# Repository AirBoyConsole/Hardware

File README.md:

# Hardware

|revision|sound|input|EEPROM|
|:---:|:---:|:---:|:---:|
| A | PCM5100A + LM4936 | MCP23008 | 128kb |

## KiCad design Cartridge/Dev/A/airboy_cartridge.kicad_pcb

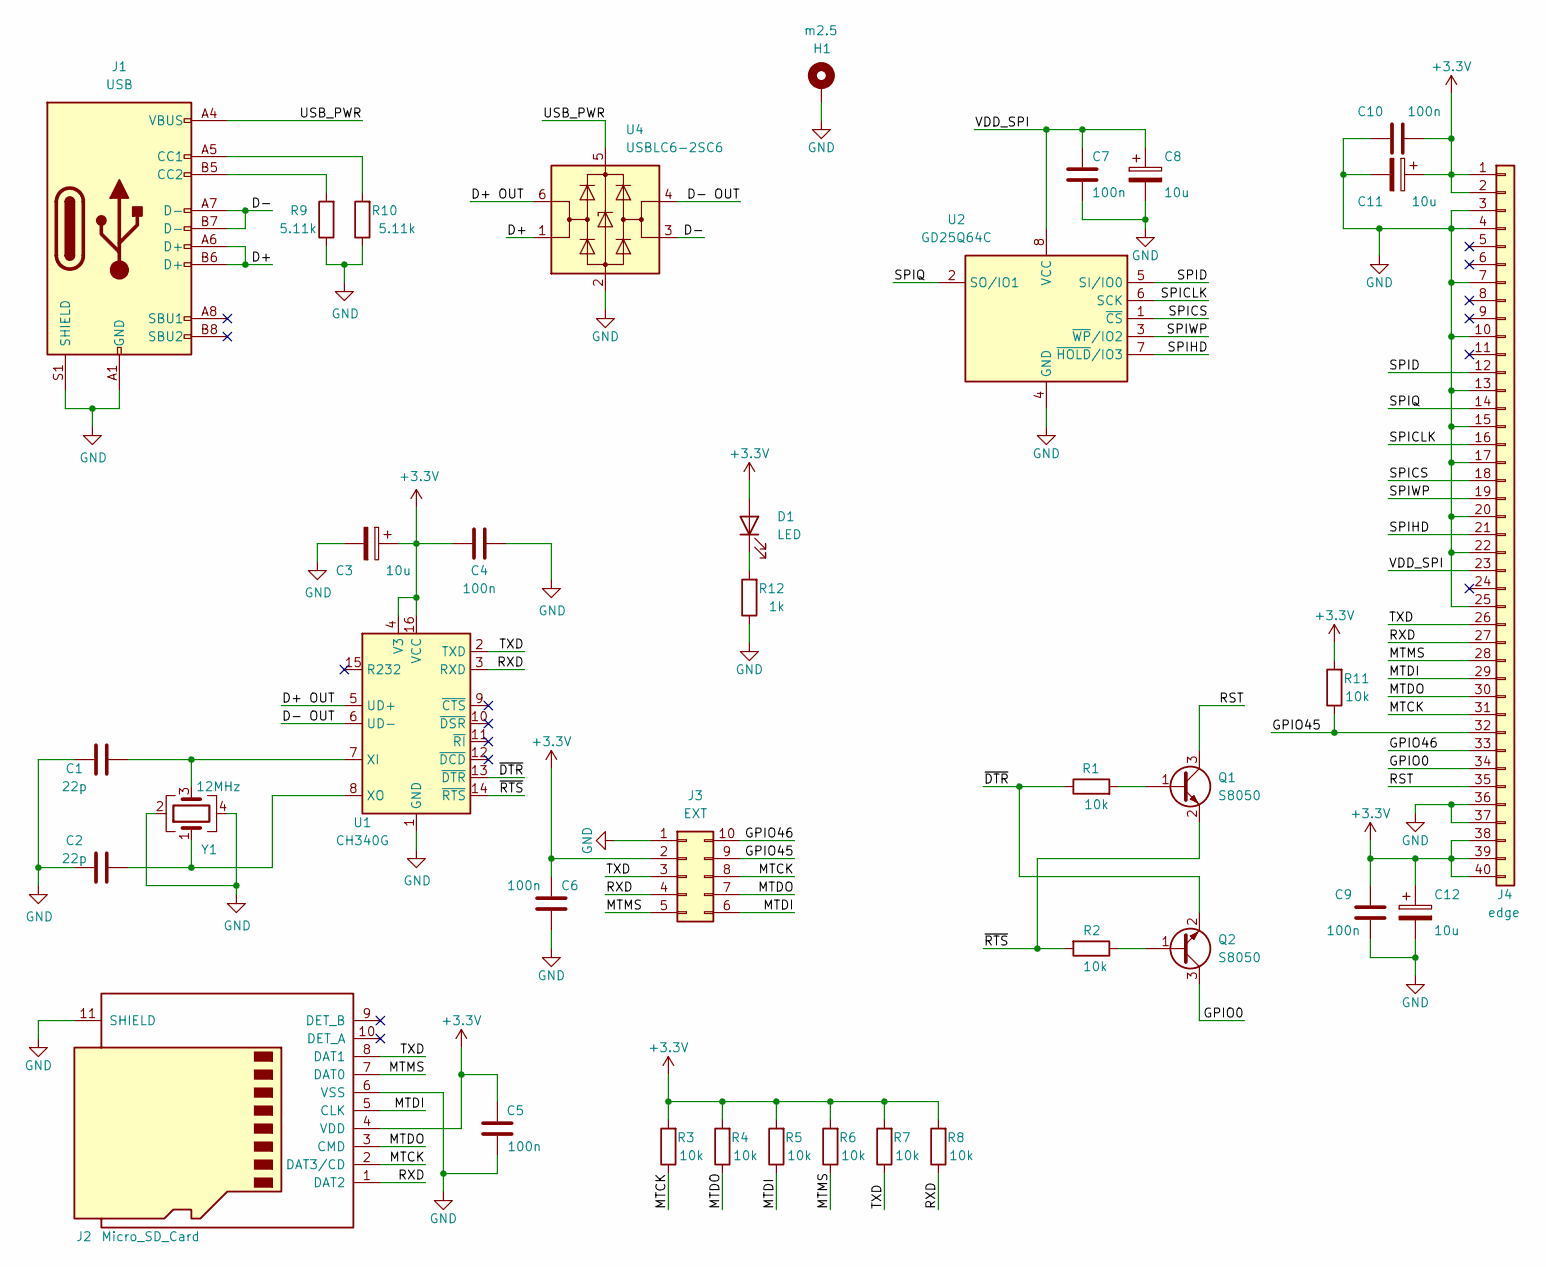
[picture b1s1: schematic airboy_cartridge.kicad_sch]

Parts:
C1, C2: 22p; C_0603_1608Metric_Pad1.08x0.95mm_HandSolder
C3, C8, C11, C12: 10u; CP_EIA-3216-18_Kemet-A_Pad1.58x1.35mm_HandSolder
C4, C5, C6, C7, C9, C10: 100n; C_0603_1608Metric_Pad1.08x0.95mm_HandSolder
D1: LED; LED_0603_1608Metric_Pad1.05x0.95mm_HandSolder
H1: m2.5; MountingHole_2.7mm_M2.5_Pad
J1: USB; USB_C_Receptacle_Palconn_UTC16-G
J2: Micro_SD_Card; microSD_HC_Hirose_DM3D-SF
J3: EXT; PinHeader_2x05_P2.54mm_Vertical
J4: edge; Connector
Q1, Q2: S8050; SOT-23
R1, R2, R3, R4, R5, R6, R7, R8, R11: 10k; R_0603_1608Metric_Pad0.98x0.95mm_HandSolder
R9, R10: 5.11k; R_0603_1608Metric_Pad0.98x0.95mm_HandSolder
R12: 1k; R_0603_1608Metric_Pad0.98x0.95mm_HandSolder
U1: CH340G; SOIC-16_3.9x9.9mm_P1.27mm
U2: GD25Q64C; SOP-8_5.28x5.23mm_P1.27mm
U4: USBLC6-2SC6; SOT-23-6
Y1: 12MHz; Crystal_SMD_5032-4Pin_5.0x3.2mm

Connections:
+3.3V: C3.1, C4.1, C5.1, C6.1, C9.2, C10.2, C11.1, C12.1, D1.2 (A), J2.4 (VDD), J3.2, J4.1, J4.2, J4.38, J4.39, J4.40, R3.2, R4.2, R5.2, R6.2, R7.2, R8.2, R11.2, U1.4 (V3), U1.16 (VCC)
/D+: J1.A6 (D+), J1.B6 (D+), U4.1 (I/O1)
/D+ OUT: U1.5 (UD+), U4.6 (I/O1)
/D-: J1.A7 (D-), J1.B7 (D-), U4.3 (I/O2)
/D- OUT: U1.6 (UD-), U4.4 (I/O2)
/GPIO0: J4.34, Q2.3 (C)
/GPIO45: J3.9, J4.32, R11.1
/GPIO46: J3.10, J4.33
/MTCK: J2.2 (DAT3/CD), J3.8, J4.31, R3.1
/MTDI: J2.5 (CLK), J3.6, J4.29, R5.1
/MTDO: J2.3 (CMD), J3.7, J4.30, R4.1
/MTMS: J2.7 (DAT0), J3.5, J4.28, R6.1
/RST: J4.35, Q1.3 (C)
/RXD: J2.1 (DAT2), J3.4, J4.27, R8.1, U1.3 (RXD)
/SPICLK: J4.16, U2.6 (SCK)
/SPICS: J4.18, U2.1 (~CS)
/SPID: J4.12, U2.5 (SI/IO0)
/SPIHD: J4.21, U2.7 (~HOLD/IO3)
/SPIQ: J4.14, U2.2 (SO/IO1)
/SPIWP: J4.19, U2.3 (~WP/IO2)
/TXD: J2.8 (DAT1), J3.3, J4.26, R7.1, U1.2 (TXD)
/USB_PWR: J1.A4 (VBUS), J1.A9 (VBUS), J1.B4 (VBUS), J1.B9 (VBUS), U4.5 (VBUS)
/VDD_SPI: C7.1, C8.1, J4.23, U2.8 (VCC)
/~DTR: Q2.2 (E), R1.1, U1.13 (~DTR)
/~RTS: Q1.2 (E), R2.2, U1.14 (~RTS)
GND: C1.2, C2.2, C3.2, C4.2, C5.2, C6.2, C7.2, C8.2, C9.1, C10.1, C11.2, C12.2, H1.1, J1.A1 (GND), J1.A12 (GND), J1.B1 (GND), J1.B12 (GND), J1.S1 (SHIELD), J2.6 (VSS), J2.11 (SHIELD), J3.1, J4.3, J4.4, J4.7, J4.10, J4.13, J4.15, J4.17, J4.20, J4.22, J4.25, J4.36, J4.37, R9.1, R10.1, R12.1, U1.1 (GND), U2.4 (GND), U4.2 (GND), Y1.2, Y1.4
unnamed: C1.1, U1.7 (XI), Y1.3
unnamed: C2.1, U1.8 (XO), Y1.1
unnamed: D1.1 (K), R12.2
unnamed: J1.A5 (CC1), R10.2
unnamed: J1.B5 (CC2), R9.2
unnamed: Q1.1 (B), R1.2
unnamed: Q2.1 (B), R2.1

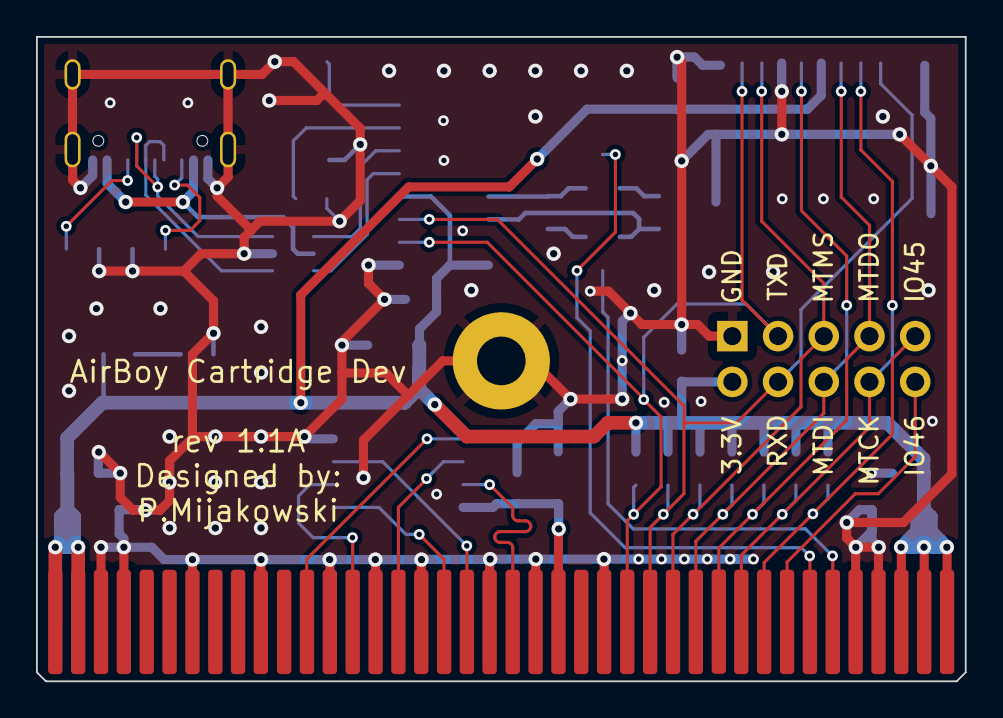
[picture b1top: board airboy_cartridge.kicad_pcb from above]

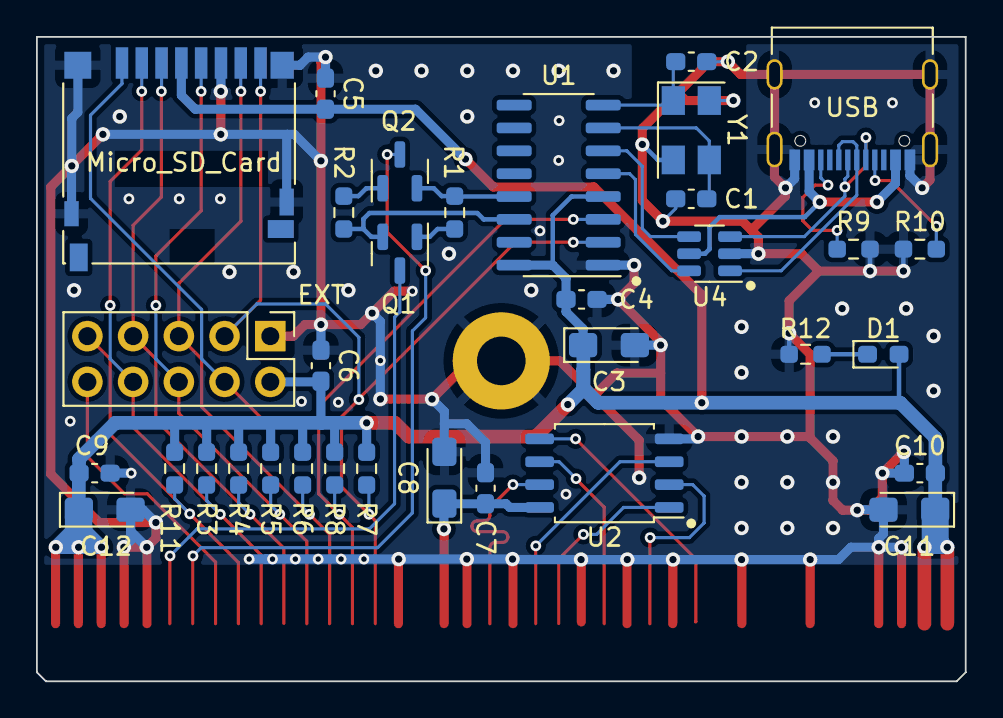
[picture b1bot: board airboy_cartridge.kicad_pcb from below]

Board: 2 copper layers, 51.6 x 35.8 mm, 36 parts (35 on the bottom side), 33 nets.

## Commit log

2023-04-03 First version commit
2023-04-03 info changes
2023-04-03 modified PCB and output gerber files
